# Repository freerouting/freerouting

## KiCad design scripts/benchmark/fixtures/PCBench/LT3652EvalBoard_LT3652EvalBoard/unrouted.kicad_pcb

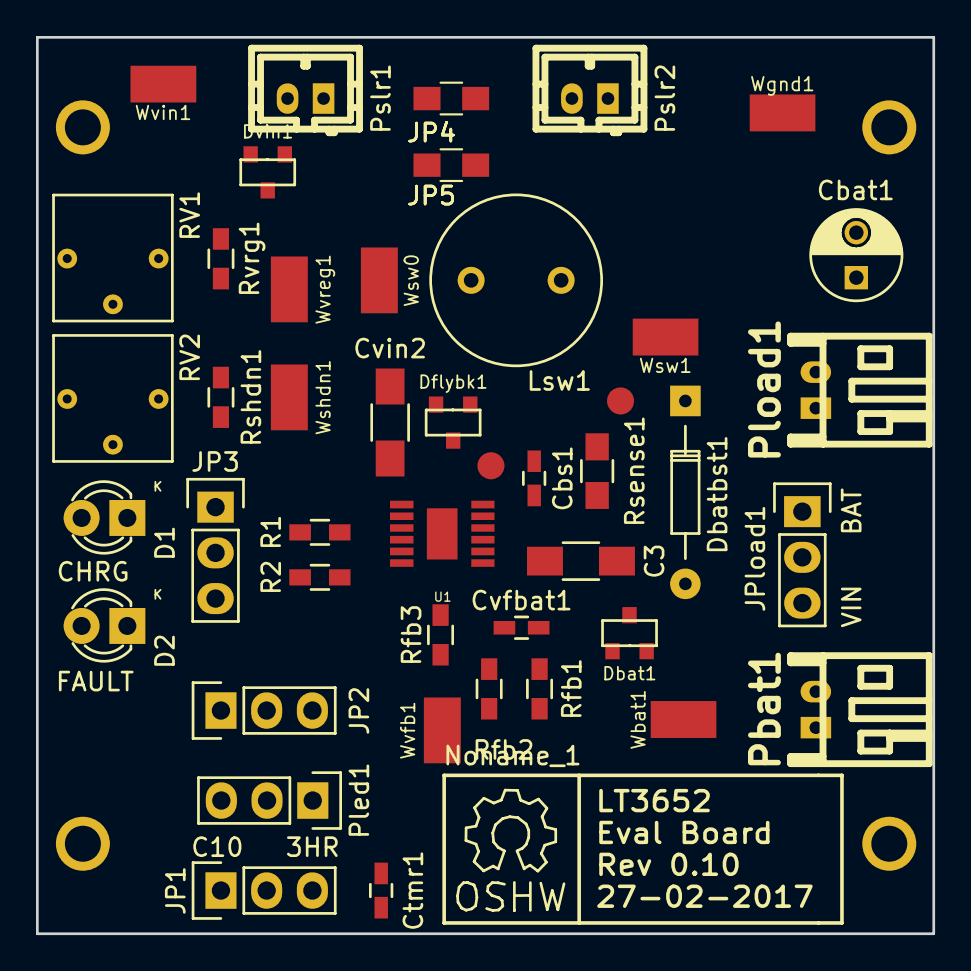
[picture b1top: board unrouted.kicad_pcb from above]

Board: 2 copper layers, 49.8 x 49.8 mm, 46 parts (0 on the bottom side), 26 nets, no tracks yet.

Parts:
C3: 10uF; C_1206_HandSoldering
Cbat1: 100uF; C_Radial_D5_L6_P2.5
Cbs1: 1uF; C_0603_HandSoldering
Ctmr1: 0.68µF; C_0603_HandSoldering
Cvfbat1: 22pF; C_0603_HandSoldering
Cvin2: 10uF; C_1206_HandSoldering
D1: 3mm GRN; LED-3MM
D2: 3mm RED; LED-3MM
Dbat1: D_Schottky_Small_ZLLS500; DIODES_INC_ZLLS500
Dbatbst1: D_Small; Diode_DO-35_SOD27_Horizontal_RM10
Dflybk1: ZLLS500; DIODES_INC_ZLLS500
Dvin1: ZLLS500; DIODES_INC_ZLLS500
JP1: TIMER OPT; Pin_Header_Straight_1x03
JP2, JP3: JUMPER3; Pin_Header_Straight_1x03
JP4: Jumper_NO_Small; R_0805_HandSoldering
JP5: Jumper_NC_Small; R_0805_HandSoldering
JPload1: JUMPER3; Pin_Header_Straight_1x03
Lsw1: 10uH; PANASONIC_ELC09D100F
Noname_1: Symbol_OSHW-Logo_SilkScreen
Pbat1: JST PH; s2b-ph-kl
Pled1: CONN_01X03; Pin_Header_Straight_1x03
Pload1: JST PH; s2b-ph-kl
Pslr1, Pslr2: JST PH; b2b-ph-kl
R1, R2: 10K; R_0603_HandSoldering
RV1, RV2: POT; Bourns_3362P_Trimmer
Rfb1: 90k; R_0603_HandSoldering
Rfb2: 330k; R_0603_HandSoldering
Rfb3: 179k; R_0603_HandSoldering
Rsense1: 250mO; R_0805_HandSoldering
Rshdn1: 10K; R_0603_HandSoldering
Rvrg1: 10K; R_0603_HandSoldering
U1: LT3652; LT3652MSE_HandSoldering
Wbat1: TEST_1P; HARWIN_S1751-46
Wbst1: TEST_1P; Measurement_Point_Round-SMD-Pad_Small
Wgnd1: TEST_1P; HARWIN_S1751-46
Wshdn1: TEST_1P; HARWIN_S1751-46
Wsw0, Wsw1: TEST_1P; HARWIN_S1751-46
Wsw2: TEST_1P; Measurement_Point_Round-SMD-Pad_Small
Wvfb1: TEST_1P; HARWIN_S1751-46
Wvin1: TEST_1P; HARWIN_S1751-46
Wvreg1: TEST_1P; HARWIN_S1751-46

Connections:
/BAT: C3.1, Cvfbat1.1, Dbat1.3, Dbatbst1.2, JPload1.1, Pbat1.2, Rfb1.1, Rsense1.2, U1.9, Wbat1.1
/BOOST: Cbs1.1, Dbatbst1.1, U1.11, Wbst1.1
/SENSE: Lsw1.2, Rsense1.1, U1.10, Wsw1.1
/SHDN: RV2.2, U1.3, Wshdn1.1
/SW: Cbs1.2, Dflybk1.1, Lsw1.1, U1.12, Wsw0.1, Wsw2.1
/VFB: Cvfbat1.2, Rfb3.2, U1.7, Wvfb1.1
/VIN: Cvin2.2, D1.2, D2.2, Dbat1.1, Dvin1.1, JPload1.3, Pled1.1, RV1.1, RV2.1, U1.1, Wvin1.1
/VIN_REG: RV1.2, U1.2, Wvreg1.1
GND: C3.2, Cbat1.2, Ctmr1.2, Cvin2.1, Dflybk1.3, JP1.1, JP5.1, Pbat1.1, Pload1.1, Pslr2.1, Rfb2.2, Rshdn1.2, Rvrg1.2, U1.13, Wgnd1.1
unnamed: Cbat1.1, JPload1.2, Pload1.2
unnamed: Ctmr1.1, JP1.3
unnamed: D1.1, JP3.1
unnamed: D2.1, JP2.1
unnamed: Dvin1.3, Pslr1.2
unnamed: JP1.2, U1.6
unnamed: JP2.2, R2.2
unnamed: JP2.3, Pled1.2
unnamed: JP3.2, R1.2
unnamed: JP3.3, Pled1.3
unnamed: JP4.1, JP5.2, Pslr1.1
unnamed: JP4.2, Pslr2.2
unnamed: R1.1, U1.4
unnamed: R2.1, U1.5
unnamed: RV1.3, Rvrg1.1
unnamed: RV2.3, Rshdn1.1
unnamed: Rfb1.2, Rfb2.1, Rfb3.1

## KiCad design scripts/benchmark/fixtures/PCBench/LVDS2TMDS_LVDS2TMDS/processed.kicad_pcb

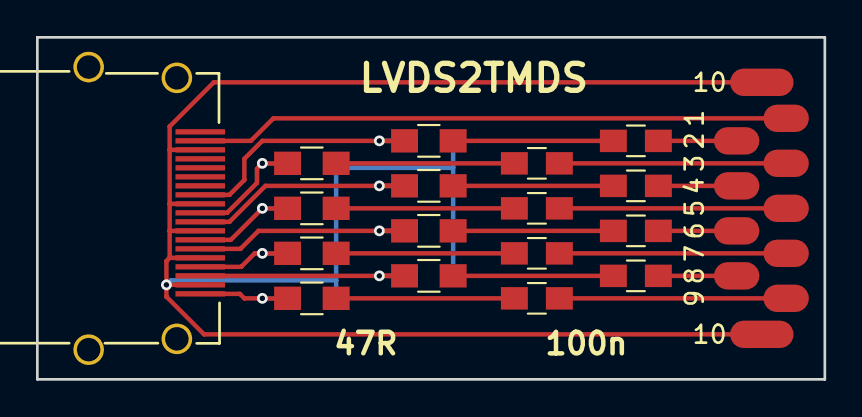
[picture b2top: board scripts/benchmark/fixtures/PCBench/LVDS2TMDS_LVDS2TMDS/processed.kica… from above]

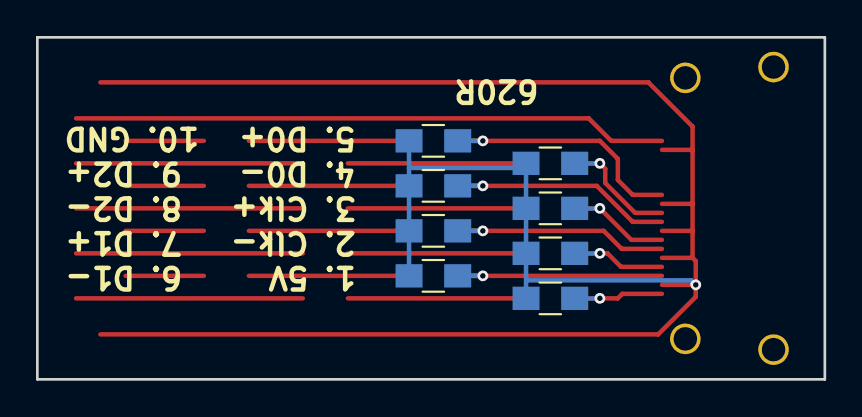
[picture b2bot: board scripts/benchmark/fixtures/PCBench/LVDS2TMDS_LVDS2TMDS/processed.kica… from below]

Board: 2 copper layers, 43.8 x 19.0 mm, 26 parts (8 on the bottom side), 26 nets.

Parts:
C1, C2, C3, C4, C5, C6, C7, C8: 100n; C_0805_HandSoldering
J1: HDMI; hdmi_new
P1: CONN_01X10; 10pinSolderpads
R1, R2, R5, R6, R9, R10, R13, R14: 47R; R_0805_HandSoldering
R3, R4, R7, R8, R11, R12, R15, R16: 620R; R_0805_HandSoldering

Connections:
+5V: J1.18, P1.1
GND: J1.2, J1.5, J1.8, J1.11, J1.17, P1.10, R3.1, R4.1, R7.1, R8.1, R11.1, R12.1, R15.1, R16.1
unnamed: C1.1, P1.2
unnamed: C1.2, R1.1
unnamed: C2.1, P1.3
unnamed: C2.2, R2.1
unnamed: C3.1, P1.4
unnamed: C3.2, R5.1
unnamed: C4.1, P1.5
unnamed: C4.2, R6.1
unnamed: C5.1, P1.6
unnamed: C5.2, R9.1
unnamed: C6.1, P1.7
unnamed: C6.2, R10.1
unnamed: C7.1, P1.8
unnamed: C7.2, R13.1
unnamed: C8.1, P1.9
unnamed: C8.2, R14.1
unnamed: J1.1, R14.2, R16.2
unnamed: J1.3, R13.2, R15.2
unnamed: J1.4, R10.2, R12.2
unnamed: J1.6, R9.2, R11.2
unnamed: J1.7, R6.2, R8.2
unnamed: J1.9, R5.2, R7.2
unnamed: J1.10, R2.2, R4.2
unnamed: J1.12, R1.2, R3.2

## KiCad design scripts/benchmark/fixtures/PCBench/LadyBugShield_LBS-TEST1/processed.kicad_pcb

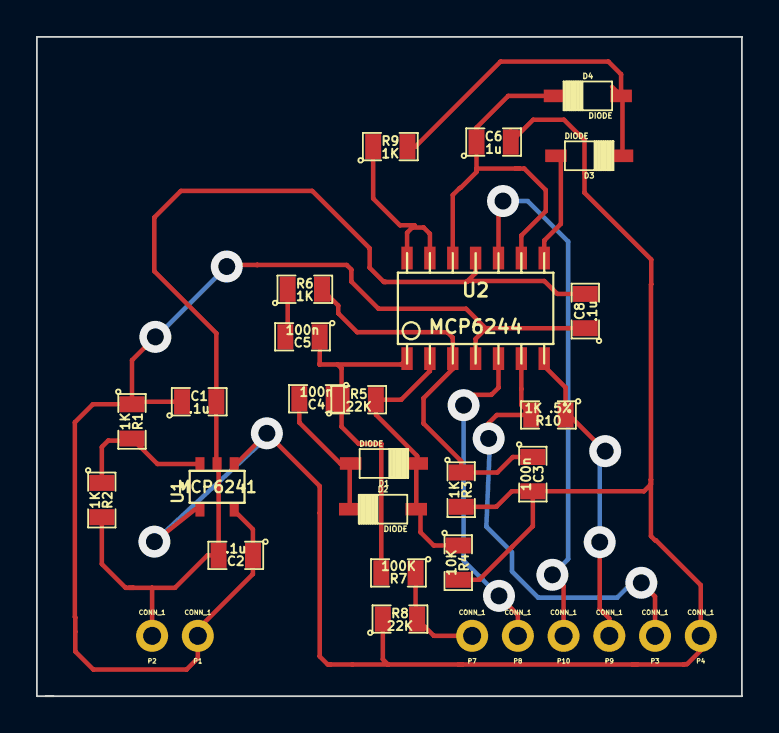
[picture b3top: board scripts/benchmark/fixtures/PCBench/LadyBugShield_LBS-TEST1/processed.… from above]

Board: 2 copper layers, 39.2 x 36.6 mm, 31 parts (0 on the bottom side), 18 nets.

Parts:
C1, C2, C8: .1u; SM0805
C3, C4, C5: 100n; SM0805
C6: 1u; SM0805
D1, D2, D3, D4: DIODE; SOD-123
P1, P2, P3, P4, P7, P8, P9, P10: CONN_1; LB_CONN_1
R1, R2, R3, R6, R9: 1K; SM0805
R4: 10K; SM0805
R5, R8: 22K; SM0805
R7: 100K; SM0805
R10: 1K .5%; SM0805
U1: MCP6241; SOT23-5
U2: MCP6244; LB_MCP6244

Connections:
5+V: C1.1, C2.1, C8.1, P1.1, R1.1, U1.5, U2.4
/ConvertToDigital/EC_AIN: R9.1, U2.13, U2.14
/ConvertToDigital/VGND: C3.2, C6.2, P4.1, R3.2, R4.2, R8.1, U1.1, U1.4
/GainLoop/AC_SHRUNK: P8.1, U2.5
/GainLoop/EC_ProbeIN: P3.1, R10.2, U2.6
/GainLoop/EC_SIGNAL: P9.1, R10.1, U2.7
/Rectify/DD: D3.2, D4.1, R9.2
/Rectify/EC_SIGNAL: P10.1, U2.10
/Rectify/RVin-: C6.1, D4.2, U2.9, U2.12
/Rectify/R_Vout: D3.1, U2.8
/VIn/AC_SHRUNK: P7.1, R7.1, R8.2
/VIn/G1: C4.2, D1.1, D2.2
/VIn/OSC_Vin+: C3.1, R3.1, R6.2, U2.3
/VIn/OSC_Vin-: D1.2, D2.1, R4.1, R5.2, U2.2
/VIn/OSC_Vout: C4.1, C5.1, R5.1, R7.2, U2.1
/VIn/VGND_V+: R1.2, R2.1, U1.3
/VIn/f1: C5.2, R6.1
PGND: C1.2, C2.2, C8.2, P2.1, R2.2, U1.2, U2.11

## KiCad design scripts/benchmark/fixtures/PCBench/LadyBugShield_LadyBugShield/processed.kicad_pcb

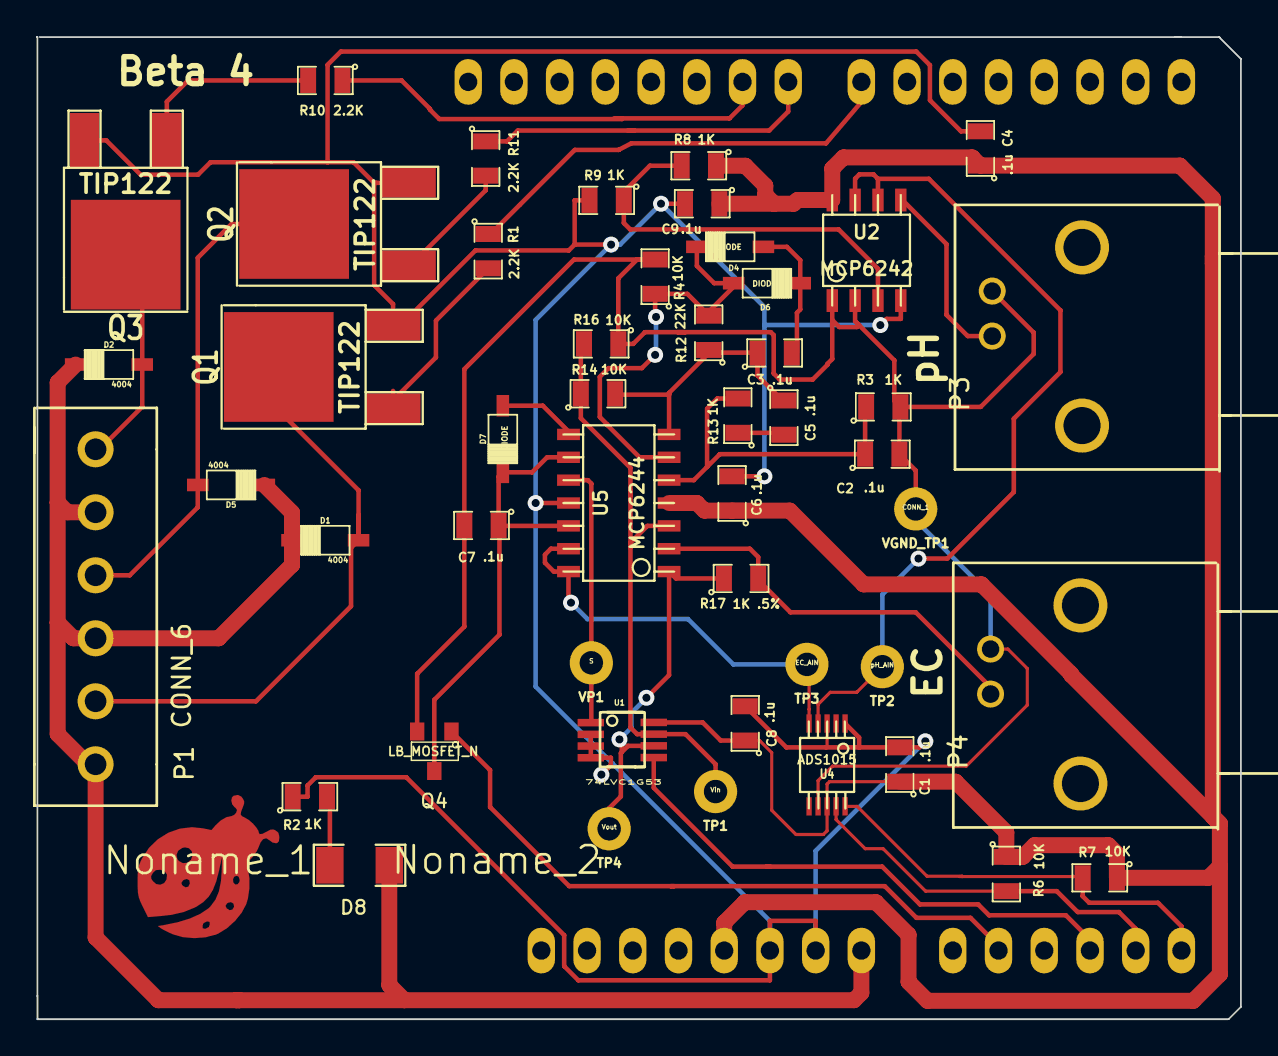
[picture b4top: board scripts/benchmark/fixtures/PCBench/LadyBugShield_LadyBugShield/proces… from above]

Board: 2 copper layers, 66.9 x 54.6 mm, 51 parts (0 on the bottom side), 33 nets.

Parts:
ARD1: ArduinoLettuceBuddy
C1, C2, C3, C4, C5, C6, C7, C8, C9: .1u; SM0805
D1, D2, D5: 4004; SOD-123
D4, D6, D7: DIODE; SOD-123
D8: LED; SM1206
Noname_1: LadybugLogo
Noname_2: OSHW_SM
P1: CONN_6; LB_CONN_6
P3, P4: BNC; LB_BNC
Q1, Q2, Q3: TIP122; DPAK2
Q4: LB_MOSFET_N; LB_MOSFET
R1, R10, R11: 2.2K; SM0805
R2, R3, R8, R9, R13: 1K; SM0805
R4, R6, R7, R14, R16: 10K; SM0805
R12: 22K; SM0805
R17: 1K .5%; SM0805
TP1: Vin; LB_TestPoint
TP2: pH_AIN; LB_TestPoint
TP3: EC_AIN; LB_TestPoint
TP4: Vout; LB_TestPoint
U1: 74LVC1G53; LB_TSSOP8
U2: MCP6242; so-8
U4: ADS1015; msoic-10
U5: MCP6244; LB_MCP6244
VGND_TP1: CONN_1; LB_TestPoint
VP1: S; LB_TestPoint

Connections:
/Arduino/12V: ARD1.4, D1.2, D2.2, D5.2, D8.1, P1.1, P1.3, P1.5
/Arduino/FET_pin: ARD1.6, Q4.G
/Arduino/MUX_out_pin: ARD1.8, U1.5
/Arduino/SCL: ARD1.10, R7.2, U4.10
/Arduino/SDA: ARD1.9, R6.2, U4.9
/Arduino/pump1_pin: ARD1.18, R1.1
/Arduino/pump2_pin: ARD1.19, R11.1
/Arduino/pump3_pin: ARD1.20, R10.1
/DigitalAccess/EC_AIN: TP3.1, U4.5, U5.13, U5.14
/DigitalAccess/pH_AIN: TP2.1, U2.6, U2.7, U4.4
/EC/AC/EC_Vin: R14.1, R16.2, TP1.1, U1.7, U5.3
/EC/AC/G1: C3.2, D4.1, D6.2
/EC/AC/W_Vin+: C2.1, R3.1, R13.2, U5.5
/EC/AC/W_Vin-: D4.2, D6.1, R4.1, R12.2, U5.6
/EC/AC/W_Vout: C3.1, C5.1, R12.1, R14.2, U5.7
/EC/AC/f1: C5.2, R13.1
/EC/ECGain/EC_Vout: R17.1, TP4.1, U1.6, U5.1
/EC/EC_ProbeIN: P4.1, R17.2, U5.2
/EC/Rectify/RVin-: C7.1, D7.2, Q4.D, U5.9, U5.12
/EC/Rectify/R_Vout: D7.1, U5.8
/EC/Rectify/Signal: U1.1, U5.10, VP1.1
/Power/VGND_V+: R8.2, R9.1, U2.3
/Pumps/pump1: D1.1, P1.2, Q1.2
/Pumps/pump2: D5.1, P1.4, Q2.2
/Pumps/pump3: D2.1, P1.6, Q3.2
/pH/pH_ProbeIN: P3.1, U2.5
GND: ARD1.2, ARD1.3, C1.2, C4.2, C6.2, C8.2, C9.2, Q1.3, Q2.3, Q3.3, R2.1, R9.2, U1.2, U1.3, U1.4, U2.4, U4.1, U4.3, U5.11
unnamed: D8.2, R2.2
unnamed: Q1.1, R1.2
unnamed: Q2.1, R11.2
unnamed: Q3.1, R10.2
VGND: C2.2, C7.2, P3.2, P4.2, Q4.S, R3.2, R4.2, R16.1, U2.1, U2.2, U4.7, VGND_TP1.1
Vclean: ARD1.1, C1.1, C4.1, C6.1, C8.1, C9.1, R6.1, R7.1, R8.1, U1.8, U2.8, U4.8, U5.4
